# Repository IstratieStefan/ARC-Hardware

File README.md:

# ARC-Hardware
Hardware repo for ARC

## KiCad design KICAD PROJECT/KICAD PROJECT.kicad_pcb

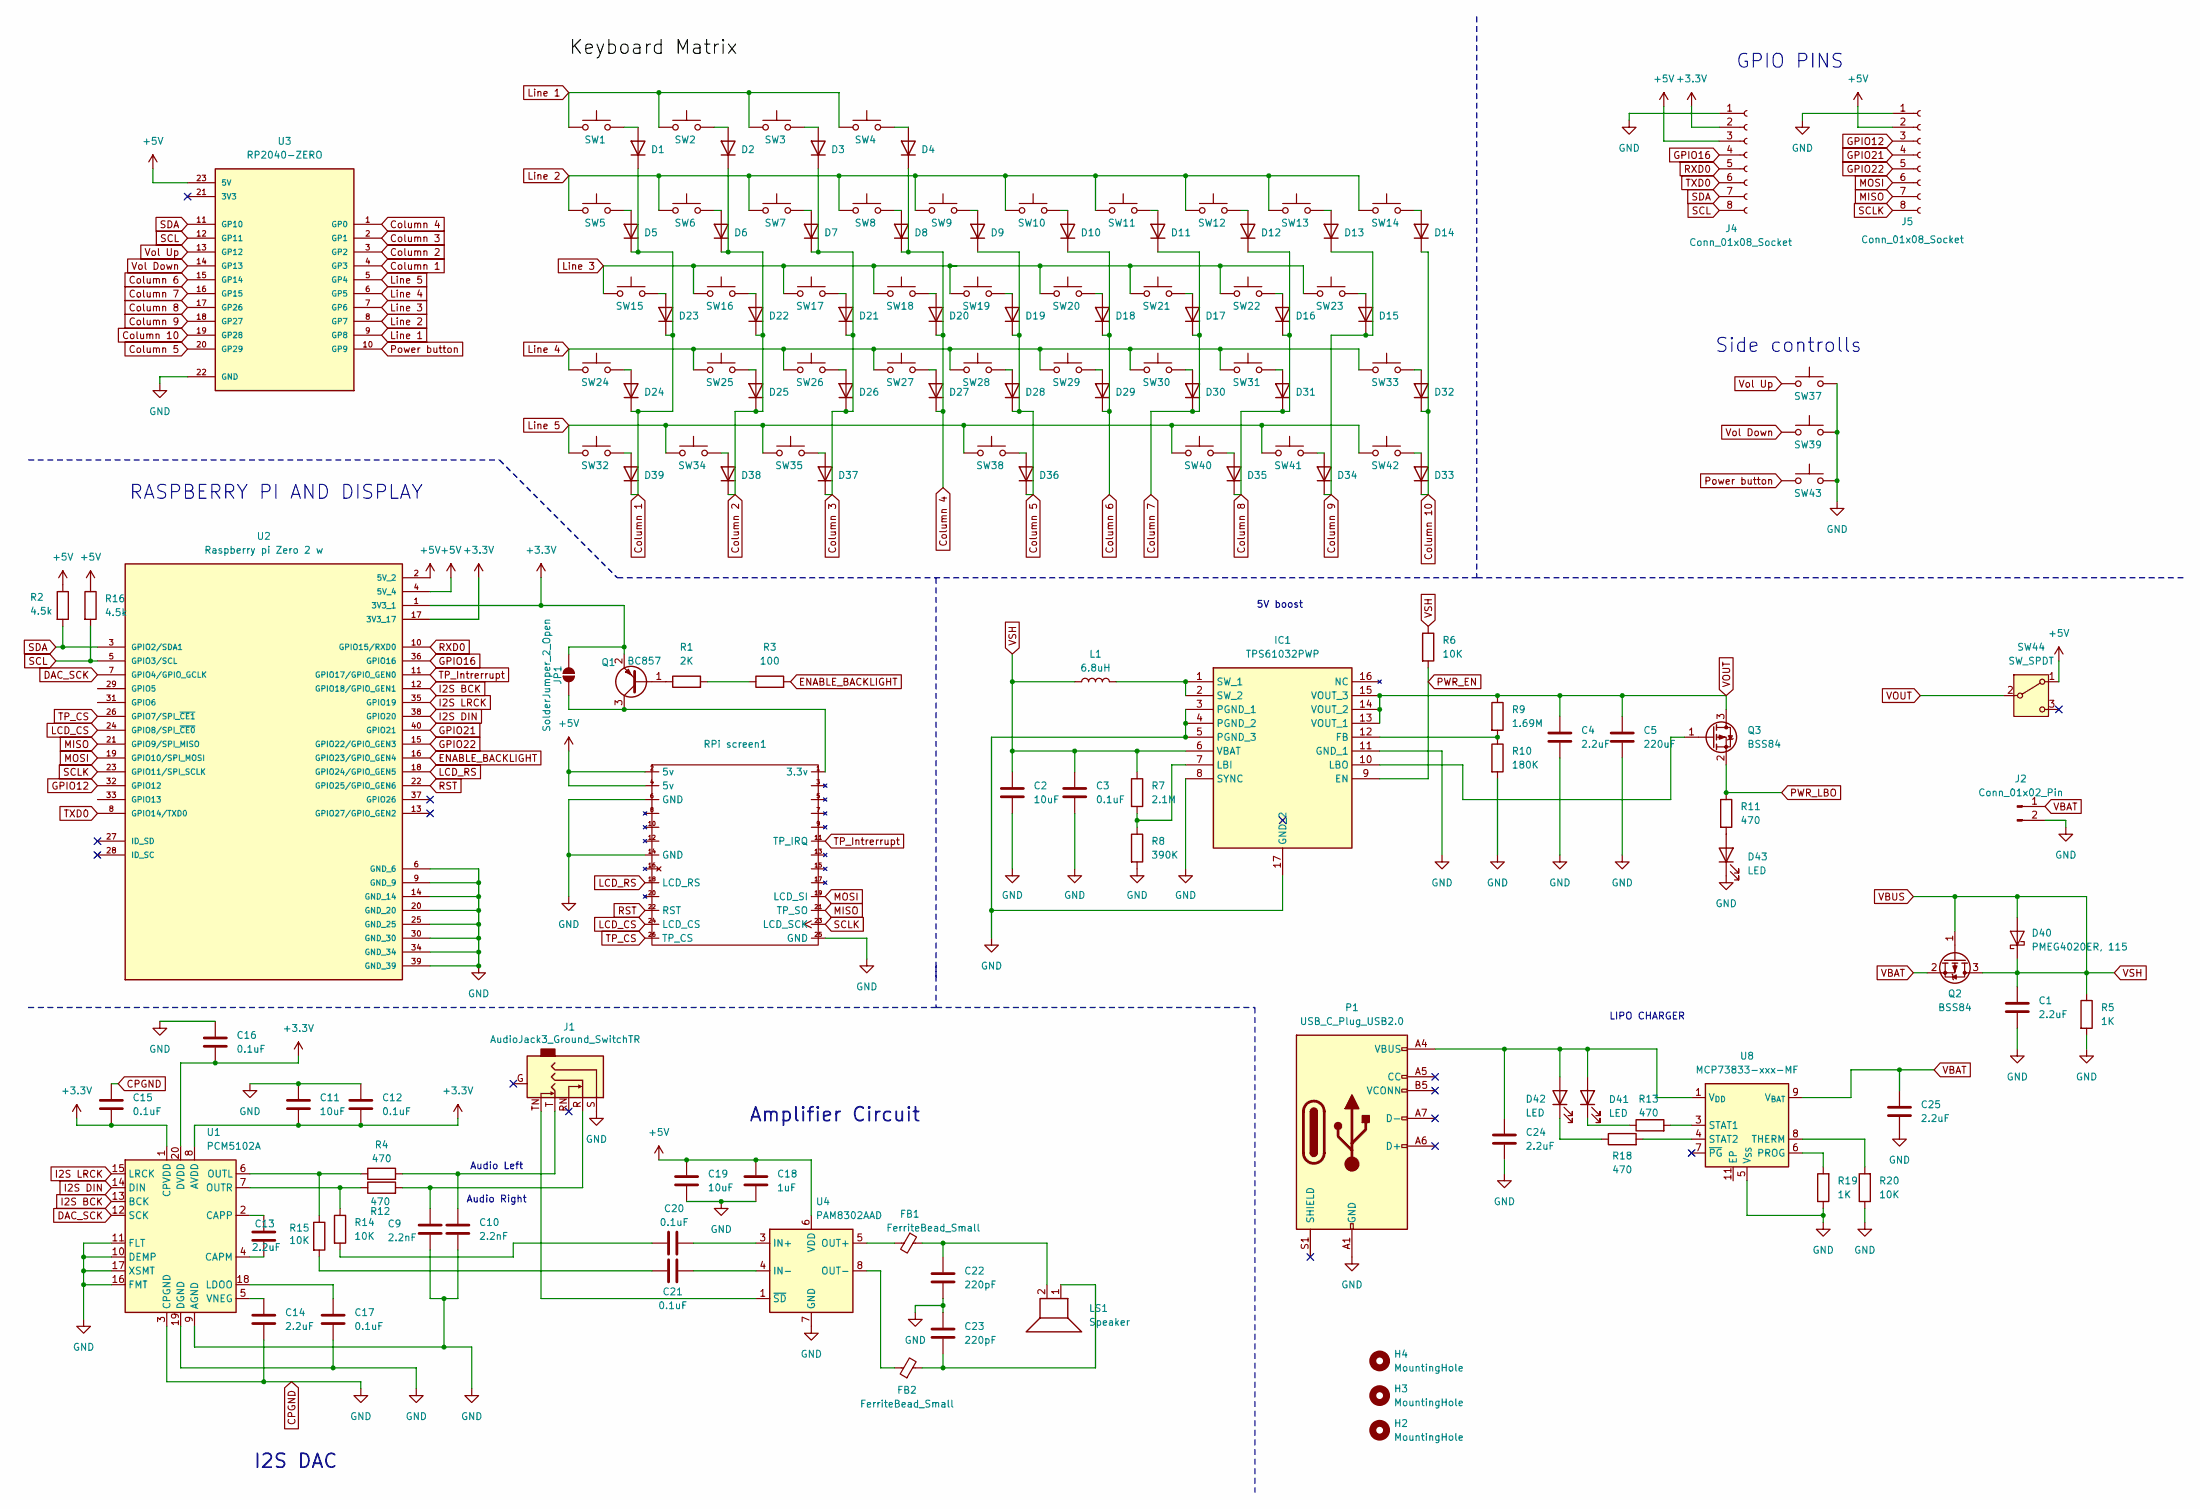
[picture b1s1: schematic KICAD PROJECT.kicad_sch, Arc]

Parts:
C1, C4, C13, C14, C24, C25: 2.2uF; C_0603_1608Metric_Pad1.08x0.95mm_HandSolder
C2, C11, C19: 10uF; C_0805_2012Metric_Pad1.18x1.45mm_HandSolder
C3, C12, C15, C16, C17, C20, C21: 0.1uF; C_0603_1608Metric_Pad1.08x0.95mm_HandSolder
C5: 220uF; C_1210_3225Metric_Pad1.33x2.70mm_HandSolder
C9, C10: 2.2nF; C_0603_1608Metric_Pad1.08x0.95mm_HandSolder
C18: 1uF; C_0603_1608Metric_Pad1.08x0.95mm_HandSolder
C22, C23: 220pF; C_0603_1608Metric_Pad1.08x0.95mm_HandSolder
D1, D2, D3, D4, D5, D6, D7, D8, D9, D10, D11, D12, D13, D14, D15, D16, D17, D18, D19, D20, D21, D22, D23, D24, D25, D26, D27, D28, D29, D30, D31, D32, D33, D34, D35, D36, D37, D38, D39: 1N4148W; D_0603_1608Metric_Pad1.05x0.95mm_HandSolder
D40: PMEG4020ER, 115; Nexperia_CFP3_SOD-123W
D41, D42, D43: LED; LED_0805_2012Metric_Pad1.15x1.40mm_HandSolder
FB1, FB2: FerriteBead_Small; L_0603_1608Metric_Pad1.05x0.95mm_HandSolder
H2, H3, H4: MountingHole; MountingHole_2.2mm_M2_Pad
IC1: TPS61032PWP; HTSSOP-16-1EP_4.4x5mm_P0.65mm_EP3.4x5mm_Mask2.66x2.46mm; Mouser Part Number 595-TPS61032PWP
J1: AudioJack3_Ground_SwitchTR; Jack_3.5mm_CUI_SJ2-3593D-SMT_Horizontal
J2: Conn_01x02_Pin; JST_PH_S2B-PH-K_1x02_P2.00mm_Horizontal
J4, J5: Conn_01x08_Socket; PinSocket_1x08_P2.54mm_Vertical
JP1: SolderJumper_2_Open; SolderJumper-2_P1.3mm_Open_Pad1.0x1.5mm
L1: 6.8uH; L_Bourns_SRP5030T
LS1: Speaker; JST_PH_S2B-PH-K_1x02_P2.00mm_Horizontal
P1: USB_C_Plug_USB2.0; USB_C_Receptacle_GCT_USB4125-xx-x_6P_TopMnt_Horizontal
Q1: BC857; SOT-23
Q2, Q3: BSS84; SOT-23
R1: 2K; R_0603_1608Metric_Pad0.98x0.95mm_HandSolder
R2, R16: 4.5k; R_0603_1608Metric_Pad0.98x0.95mm_HandSolder
R3: 100; R_0603_1608Metric_Pad0.98x0.95mm_HandSolder
R4, R11, R12, R13, R18: 470; R_0603_1608Metric_Pad0.98x0.95mm_HandSolder
R5, R19: 1K; R_0603_1608Metric_Pad0.98x0.95mm_HandSolder
R6, R14, R15, R20: 10K; R_0603_1608Metric_Pad0.98x0.95mm_HandSolder
R7: 2.1M; R_0603_1608Metric_Pad0.98x0.95mm_HandSolder
R8: 390K; R_0603_1608Metric_Pad0.98x0.95mm_HandSolder
R9: 1.69M; R_0603_1608Metric_Pad0.98x0.95mm_HandSolder
R10: 180K; R_0603_1608Metric_Pad0.98x0.95mm_HandSolder
RPi screen1: 3.5inch Display
SW1, SW2, SW3, SW4, SW5, SW6, SW7, SW8, SW9, SW10, SW11, SW12, SW13, SW14, SW15, SW16, SW17, SW18, SW19, SW20, SW21, SW22, SW23, SW24, SW25, SW26, SW27, SW28, SW29, SW30, SW31, SW32, SW33, SW34, SW35, SW38, SW40, SW41, SW42: SW_Push; SW_SPST_TL3342
SW37, SW39, SW43: SW_Push; SW_Tactile_SPST_Angled_PTS645Vx31-2LFS
SW44: SW_SPDT; SW_SPDT_PCM12
U1: PCM5102A; TSSOP-20_4.4x6.5mm_P0.65mm
U2: Raspberry pi Zero 2 w; Raspberry_Pi_Zero_Socketed_THT_FaceDown_MountingHoles; PARTREV April 2024
U3: RP2040-ZERO; RP2040-Tiny-smd; PARTREV NA
U4: PAM8302AAD; MSOP-8_3x3mm_P0.65mm
U8: MCP73833-xxx-MF; DFN-10-1EP_3x3mm_P0.5mm_EP1.58x2.35mm

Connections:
+3.3V: C11.2, C12.2, C15.2, C16.2, J4.2, JP1.2 (B), Q1.2 (E), U1.1 (CPVDD), U1.8 (AVDD), U1.20 (DVDD), U2.1 (3V3_1), U2.17 (3V3_17)
+5V: C18.1, C19.1, J4.3, J5.2, R2.1, R16.1, RPi screen1.2 (5v), RPi screen1.4 (5v), SW44.1 (A), U2.2 (5V_2), U2.4 (5V_4), U3.23 (5V), U4.6 (VDD)
CPGND: C1.2, C2.2, C3.2, C4.2, C5.2, C9.2, C10.2, C11.1, C12.1, C14.2, C15.1, C16.1, C17.2, C18.2, C19.2, C22.2, C23.1, C24.2, C25.2, D43.1 (K), IC1.3 (PGND_1), IC1.4 (PGND_2), IC1.5 (PGND_3), IC1.8 (SYNC), IC1.11 (GND_1), IC1.17 (GND_2), J1.S, J2.2, J4.1, J5.1, P1.A1 (GND), P1.A12 (GND), P1.B1 (GND), P1.B12 (GND), R5.2, R8.2, R10.2, R19.1, R20.1, RPi screen1.6 (GND), RPi screen1.14 (GND), RPi screen1.25 (GND), SW37.2, SW39.2, SW43.2, U1.3 (CPGND), U1.9 (AGND), U1.10 (DEMP), U1.11 (FLT), U1.16 (FMT), U1.17 (XSMT), U1.19 (DGND), U2.6 (GND_6), U2.9 (GND_9), U2.14 (GND_14), U2.20 (GND_20), U2.25 (GND_25), U2.30 (GND_30), U2.34 (GND_34), U2.39 (GND_39), U3.22 (GND), U4.7 (GND), U8.5 (V_{SS})
Column 1: D1.1 (K), D5.1 (K), D23.1 (K), D24.1 (K), D39.1 (K), U3.4 (GP3)
Column 2: D2.1 (K), D6.1 (K), D22.1 (K), D25.1 (K), D38.1 (K), U3.3 (GP2)
Column 3: D3.1 (K), D7.1 (K), D21.1 (K), D26.1 (K), D37.1 (K), U3.2 (GP1)
Column 4: D4.1 (K), D8.1 (K), D20.1 (K), D27.1 (K), U3.1 (GP0)
Column 5: D9.1 (K), D19.1 (K), D28.1 (K), D36.1 (K), U3.20 (GP29)
Column 6: D10.1 (K), D18.1 (K), D29.1 (K), U3.15 (GP14)
Column 7: D11.1 (K), D17.1 (K), D30.1 (K), U3.16 (GP15)
Column 8: D12.1 (K), D16.1 (K), D31.1 (K), D35.1 (K), U3.17 (GP26)
Column 9: D13.1 (K), D15.1 (K), D34.1 (K), U3.18 (GP27)
Column 10: D14.1 (K), D32.1 (K), D33.1 (K), U3.19 (GP28)
DAC_SCK: U1.12 (SCK), U2.7 (GPIO4/GPIO_GCLK)
ENABLE_BACKLIGHT: R3.2, U2.16 (GPIO23/GPIO_GEN4)
GPIO12: J5.3, U2.32 (GPIO12)
GPIO16: J4.4, U2.36 (GPIO16)
GPIO21: J5.4, U2.40 (GPIO21)
GPIO22: J5.5, U2.15 (GPIO22/GPIO_GEN3)
I2S BCK: U1.13 (BCK), U2.12 (GPIO18/GPIO_GEN1)
I2S DIN: U1.14 (DIN), U2.38 (GPIO20)
I2S LRCK: U1.15 (LRCK), U2.35 (GPIO19)
LCD_CS: RPi screen1.24 (LCD_CS), U2.24 (GPIO8/SPI_~CE0)
LCD_RS: RPi screen1.18 (LCD_RS), U2.18 (GPIO24/GPIO_GEN5)
Line 1: SW1.1, SW2.1, SW3.1, SW4.1, U3.9 (GP8)
Line 2: SW5.1, SW6.1, SW7.1, SW8.1, SW9.1, SW10.1, SW11.1, SW12.1, SW13.1, SW14.1, U3.8 (GP7)
Line 3: SW15.1, SW16.1, SW17.1, SW18.1, SW19.1, SW20.1, SW21.1, SW22.1, SW23.1, U3.7 (GP6)
Line 4: SW24.1, SW25.1, SW26.1, SW27.1, SW28.1, SW29.1, SW30.1, SW31.1, SW33.1, U3.6 (GP5)
Line 5: SW32.1, SW34.1, SW35.1, SW38.1, SW40.1, SW41.1, SW42.1, U3.5 (GP4)
MISO: J5.7, RPi screen1.21 (TP_SO), U2.21 (GPIO9/SPI_MISO)
MOSI: J5.6, RPi screen1.19 (LCD_SI), U2.19 (GPIO10/SPI_MOSI)
unnamed: C9.1, J1.R, R12.2
unnamed: C10.1, J1.T, R4.2
unnamed: C20.1, R14.2
unnamed: C21.2, R15.2
unnamed: C22.1, FB1.1, LS1.2
unnamed: C23.2, FB2.2, LS1.1
unnamed: D1.2 (A), SW1.2
unnamed: D2.2 (A), SW2.2
unnamed: D3.2 (A), SW3.2
unnamed: D4.2 (A), SW4.2
unnamed: D5.2 (A), SW5.2
unnamed: D6.2 (A), SW6.2
unnamed: D7.2 (A), SW7.2
unnamed: D8.2 (A), SW8.2
unnamed: D9.2 (A), SW9.2
unnamed: D10.2 (A), SW10.2
unnamed: D11.2 (A), SW11.2
unnamed: D12.2 (A), SW12.2
unnamed: D13.2 (A), SW13.2
unnamed: D14.2 (A), SW14.2
unnamed: D15.2 (A), SW23.2
unnamed: D16.2 (A), SW22.2
unnamed: D17.2 (A), SW21.2
unnamed: D18.2 (A), SW20.2
unnamed: D19.2 (A), SW19.2
unnamed: D20.2 (A), SW18.2
unnamed: D21.2 (A), SW17.2
unnamed: D22.2 (A), SW16.2
unnamed: D23.2 (A), SW15.2
unnamed: D24.2 (A), SW24.2
unnamed: D25.2 (A), SW25.2
unnamed: D26.2 (A), SW26.2
unnamed: D27.2 (A), SW27.2
unnamed: D28.2 (A), SW28.2
unnamed: D29.2 (A), SW29.2
unnamed: D30.2 (A), SW30.2
unnamed: D31.2 (A), SW31.2
unnamed: D32.2 (A), SW33.2
unnamed: D33.2 (A), SW42.2
unnamed: D34.2 (A), SW41.2
unnamed: D35.2 (A), SW40.2
unnamed: D36.2 (A), SW38.2
unnamed: D37.2 (A), SW35.2
unnamed: D38.2 (A), SW34.2
unnamed: D39.2 (A), SW32.2
unnamed: C24.1, D41.2 (A), D42.2 (A), P1.A4 (VBUS), P1.A9 (VBUS), P1.B4 (VBUS), P1.B9 (VBUS), U8.1 (V_{DD}), U8.2 (V_{DD})
unnamed: D41.1 (K), R13.1
unnamed: D42.1 (K), R18.1
unnamed: D43.2 (A), R11.2
unnamed: IC1.12 (FB), R9.2, R10.1
unnamed: IC1.7 (LBI), R7.2, R8.1
unnamed: IC1.10 (LBO), Q3.1 (G)
unnamed: IC1.1 (SW_1), IC1.2 (SW_2), L1.2
unnamed: JP1.1 (A), Q1.3 (C), RPi screen1.1 (3.3v)
unnamed: Q1.1 (B), R1.1
unnamed: R1.2, R3.1
unnamed: C13.2, U1.4 (CAPM)
unnamed: C13.1, U1.2 (CAPP)
unnamed: C17.1, U1.18 (LDOO)
unnamed: R4.1, R15.1, U1.6 (OUTL)
unnamed: R12.1, R14.1, U1.7 (OUTR)
unnamed: C14.1, U1.5 (VNEG)
unnamed: C20.2, U4.3 (IN+)
unnamed: C21.1, U4.4 (IN-)
unnamed: FB1.2, U4.5 (OUT+)
unnamed: FB2.1, U4.8 (OUT-)
unnamed: J1.TN, U4.1 (~SD)
unnamed: R19.2, U8.6 (PROG)
unnamed: R13.2, U8.3 (STAT1)
unnamed: R18.2, U8.4 (STAT2)
unnamed: R20.2, U8.8 (THERM)
PWR_EN: IC1.9 (EN), R6.2
PWR_LBO: Q3.2 (S), R11.1
Power button: SW43.1, U3.10 (GP9)
RST: RPi screen1.22 (RST), U2.22 (GPIO25/GPIO_GEN6)
RXD0: J4.5, U2.10 (GPIO15/RXD0)
SCL: J4.8, R16.2, U2.5 (GPIO3/SCL), U3.12 (GP11)
SCLK: J5.8, RPi screen1.23 (LCD_SCK), U2.23 (GPIO11/SPI_SCLK)
SDA: J4.7, R2.2, U2.3 (GPIO2/SDA1), U3.11 (GP10)
TP_CS: RPi screen1.26 (TP_CS), U2.26 (GPIO7/SPI_~CE1)
TP_Intrerrupt: RPi screen1.11 (TP_IRQ), U2.11 (GPIO17/GPIO_GEN0)
TXD0: J4.6, U2.8 (GPIO14/TXD0)
VBAT: C25.1, J2.1, Q2.2 (S), U8.9 (V_{BAT}), U8.10 (V_{BAT})
VBUS: C1.1, C2.1, C3.1, D40.1 (K), D40.2 (A), IC1.6 (VBAT), L1.1, Q2.1 (G), Q2.3 (D), R5.1, R6.1, R7.1
VOUT: C4.1, C5.1, IC1.13 (VOUT_1), IC1.14 (VOUT_2), IC1.15 (VOUT_3), Q3.3 (D), R9.1, SW44.2 (B)
Vol Down: SW39.1, U3.14 (GP13)
Vol Up: SW37.1, U3.13 (GP12)

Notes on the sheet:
Amplifier Circuit
I2S DAC
Audio Right
GPIO PINS
RASPBERRY PI AND DISPLAY
Side controlls
Audio Left
5V boost
LIPO CHARGER

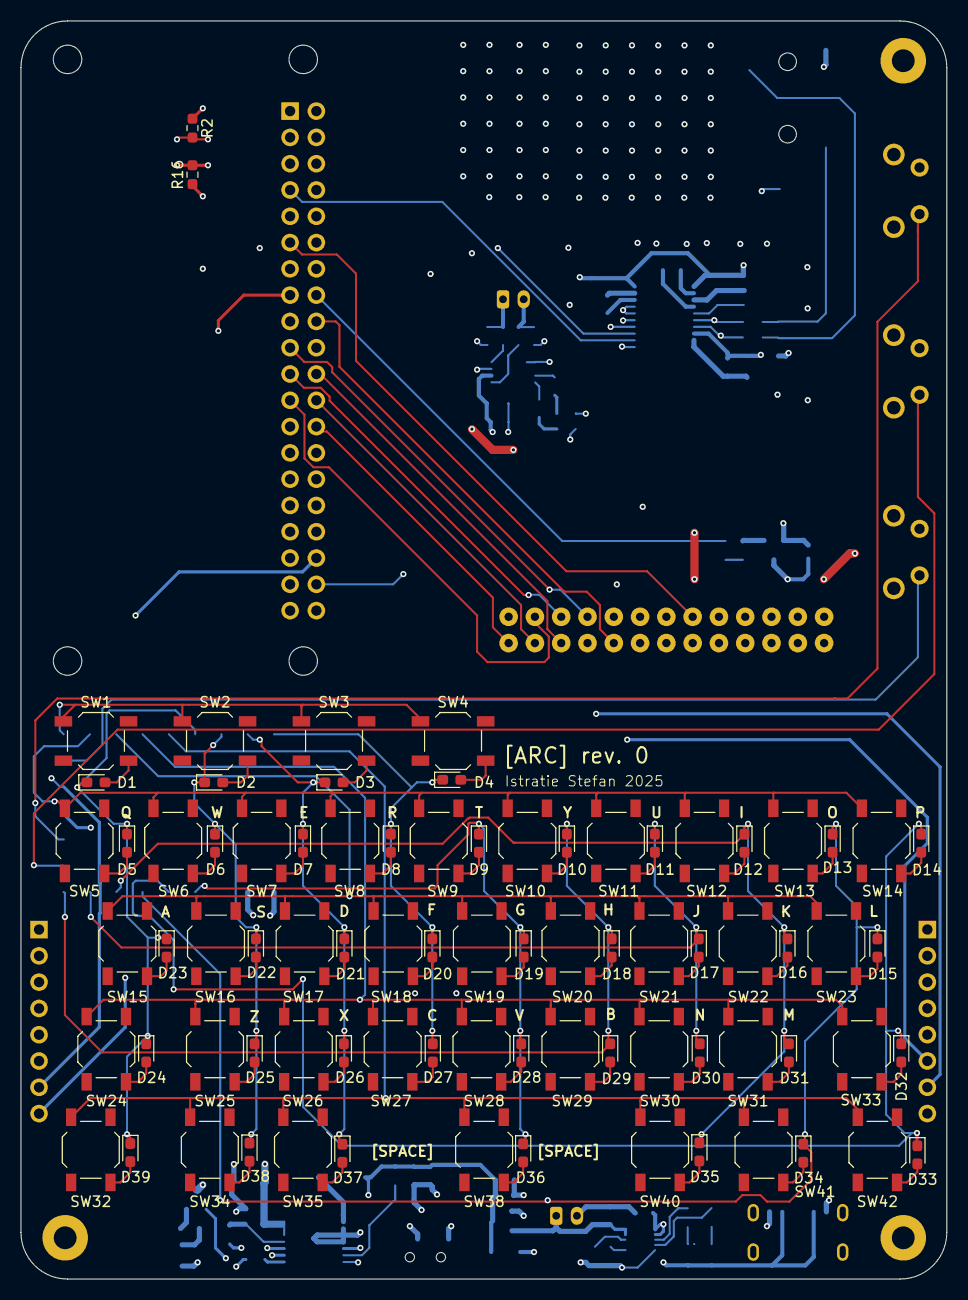
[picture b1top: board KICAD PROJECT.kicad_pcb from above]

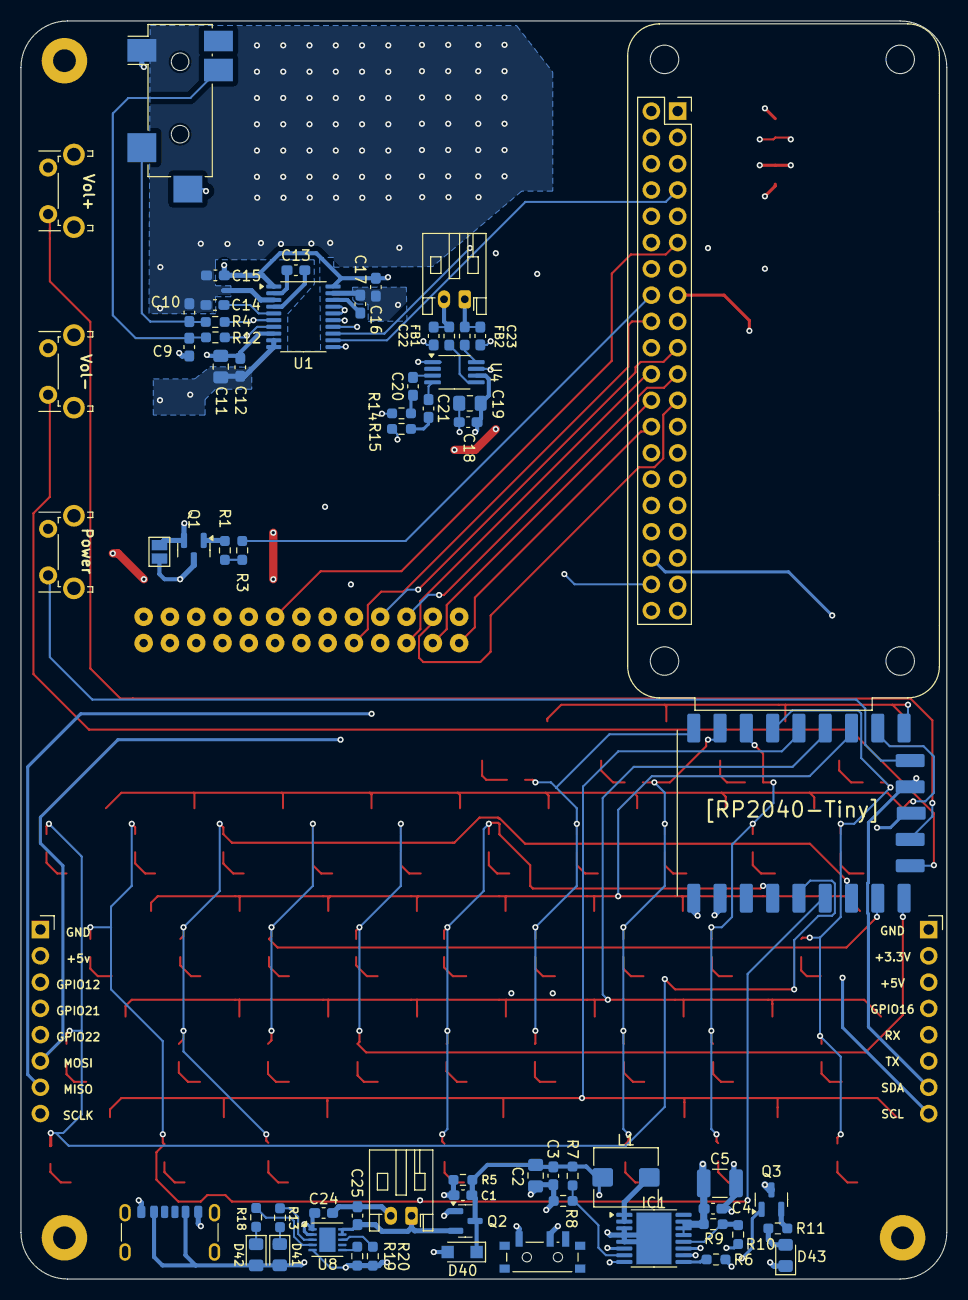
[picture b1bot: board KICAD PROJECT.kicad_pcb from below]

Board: 4 copper layers, 89.5 x 121.5 mm, 150 parts (66 on the bottom side), 118 nets.

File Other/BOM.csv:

Nr Crt.,Reference,Value,Footprint,Datasheet,Qty,DNP,Link,Exclude from BOM,Exclude from Board
1,"C1,C4,C13,C14,C24,C25",2.2uF,Capacitor_SMD:C_0603_1608Metric_Pad1.08x0.95mm_HandSolder,~,6,,,,
2,"C2,C11,C19",10uF,Capacitor_SMD:C_0805_2012Metric_Pad1.18x1.45mm_HandSolder,~,3,,,,
3,"C3,C12,C15,C16,C17,C20,C21",0.1uF,Capacitor_SMD:C_0603_1608Metric_Pad1.08x0.95mm_HandSolder,~,7,,,,
4,C5,220uF,Capacitor_SMD:C_1210_3225Metric_Pad1.33x2.70mm_HandSolder,~,1,,,,
5,"C9,C10",2.2nF,Capacitor_SMD:C_0603_1608Metric_Pad1.08x0.95mm_HandSolder,~,2,,,,
6,C18,1uF,Capacitor_SMD:C_0603_1608Metric_Pad1.08x0.95mm_HandSolder,~,1,,,,
7,"C22,C23",220pF,Capacitor_SMD:C_0603_1608Metric_Pad1.08x0.95mm_HandSolder,~,2,,,,
8,"D1,D2,D3,D4,D5,D6,D7,D8,D9,D10,D11,D12,D13,D14,D15,D16,D17,D18,D19,D20,D21,D22,D23,D24,D25,D26,D27,D28,D29,D30,D31,D32,D33,D34,D35,D36,D37,D38,D39",1N4148W,Diode_SMD:D_0603_1608Metric_Pad1.05x0.95mm_HandSolder,https://www.vishay.com/docs/85748/1n4148w.pdf,39,,,,
9,D40,"PMEG4020ER, 115",Diode_SMD:Nexperia_CFP3_SOD-123W,https://assets.nexperia.com/documents/data-sheet/PMEG4020ER.pdf,1,,,,
10,"D41,D42,D43",LED,LED_SMD:LED_0805_2012Metric_Pad1.15x1.40mm_HandSolder,~,3,,,,
11,"FB1,FB2",FerriteBead_Small,Inductor_SMD:L_0603_1608Metric_Pad1.05x0.95mm_HandSolder,~,2,,,,
12,"H2,H3,H4",MountingHole,MountingHole:MountingHole_2.2mm_M2_Pad,~,3,,,Excluded from BOM,
13,IC1,TPS61032PWP,Package_SO:HTSSOP-16-1EP_4.4x5mm_P0.65mm_EP3.4x5mm_Mask2.66x2.46mm,http://www.ti.com/lit/ds/symlink/tps61030.pdf,1,,,,
14,J1,AudioJack3_Ground_SwitchTR,Connector_Audio:Jack_3.5mm_CUI_SJ2-3593D-SMT_Horizontal,~,1,,,,
15,J2,Conn_01x02_Pin,Connector_JST:JST_PH_S2B-PH-K_1x02_P2.00mm_Horizontal,~,1,,,,
16,"J4,J5",Conn_01x08_Socket,Connector_PinSocket_2.54mm:PinSocket_1x08_P2.54mm_Vertical,~,2,,,,
17,JP1,SolderJumper_2_Open,Jumper:SolderJumper-2_P1.3mm_Open_Pad1.0x1.5mm,~,1,,,Excluded from BOM,
18,L1,6.8uH,Inductor_SMD:L_Bourns_SRP5030T,~,1,,,,
19,LS1,Speaker,Connector_JST:JST_PH_S2B-PH-K_1x02_P2.00mm_Horizontal,~,1,,,,
20,P1,USB_C_Plug_USB2.0,Connector_USB:USB_C_Receptacle_GCT_USB4125-xx-x_6P_TopMnt_Horizontal,https://www.usb.org/sites/default/files/documents/usb_type-c.zip,1,,,,
21,Q1,BC857,Package_TO_SOT_SMD:SOT-23,https://www.onsemi.com/pub/Collateral/BC860-D.pdf,1,,,,
22,"Q2,Q3",BSS84,Package_TO_SOT_SMD:SOT-23,http://assets.nexperia.com/documents/data-sheet/BSS84.pdf,2,,,,
23,R1,2K,Resistor_SMD:R_0603_1608Metric_Pad0.98x0.95mm_HandSolder,~,1,,,,
24,"R2,R16",4.5k,Resistor_SMD:R_0603_1608Metric_Pad0.98x0.95mm_HandSolder,~,2,,,,
25,R3,100,Resistor_SMD:R_0603_1608Metric_Pad0.98x0.95mm_HandSolder,~,1,,,,
26,"R4,R11,R12,R13,R18",470,Resistor_SMD:R_0603_1608Metric_Pad0.98x0.95mm_HandSolder,~,5,,,,
27,"R5,R19",1K,Resistor_SMD:R_0603_1608Metric_Pad0.98x0.95mm_HandSolder,~,2,,,,
28,R6,200K,Resistor_SMD:R_0603_1608Metric_Pad0.98x0.95mm_HandSolder,~,1,,,,
29,R7,2.1M,Resistor_SMD:R_0603_1608Metric_Pad0.98x0.95mm_HandSolder,~,1,,,,
30,R8,390K,Resistor_SMD:R_0603_1608Metric_Pad0.98x0.95mm_HandSolder,~,1,,,,
31,R9,1.69M,Resistor_SMD:R_0603_1608Metric_Pad0.98x0.95mm_HandSolder,~,1,,,,
32,R10,180K,Resistor_SMD:R_0603_1608Metric_Pad0.98x0.95mm_HandSolder,~,1,,,,
33,"R14,R15,R20",10K,Resistor_SMD:R_0603_1608Metric_Pad0.98x0.95mm_HandSolder,~,3,,,,
34,RPi screen1,~,arc:3.5inch Display,,1,,,,
35,"SW1,SW2,SW3,SW4,SW5,SW6,SW7,SW8,SW9,SW10,SW11,SW12,SW13,SW14,SW15,SW16,SW17,SW18,SW19,SW20,SW21,SW22,SW23,SW24,SW25,SW26,SW27,SW28,SW29,SW30,SW31,SW32,SW33,SW34,SW35,SW38,SW40,SW41,SW42",SW_Push,Button_Switch_SMD:SW_SPST_TL3342,~,39,,,,
36,"SW37,SW39,SW43",SW_Push,Button_Switch_THT:SW_Tactile_SPST_Angled_PTS645Vx31-2LFS,~,3,,,,
37,SW44,SW_SPDT,Button_Switch_SMD:SW_SPDT_PCM12,~,1,,,,
38,U1,PCM5102A,Package_SO:TSSOP-20_4.4x6.5mm_P0.65mm,https://www.ti.com/lit/ds/symlink/pcm5102a.pdf,1,,,,
39,U2,Raspberry pi Zero 2 w,Module:Raspberry_Pi_Zero_Socketed_THT_FaceDown_MountingHoles,,1,,,,
40,U3,RP2040-ZERO,RP2040-Tiny_kicad-main:RP2040-Tiny-smd,,1,,,,
41,U4,PAM8302AAD,Package_SO:MSOP-8_3x3mm_P0.65mm,https://www.diodes.com/assets/Datasheets/PAM8302A.pdf,1,,,,
42,U8,MCP73833-xxx-MF,Package_DFN_QFN:DFN-10-1EP_3x3mm_P0.5mm_EP1.58x2.35mm,https://ww1.microchip.com/downloads/aemDocuments/documents/O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,1,,,,

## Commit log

2025-06-22 initial 3d model
2025-06-22 reference
2025-06-23 v2 pcb
2025-06-27 Kicad Project
2025-06-29 3d files updates
    far from final bro
2025-07-13 Updates and gerbers
2025-07-25 Stl Files + Render +Organized Repo
